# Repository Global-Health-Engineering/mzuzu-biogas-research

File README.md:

# Solar Sludge Pasteurization Control System

This repository contains the engineering files, firmware, and analysis scripts for a solar-powered sludge pasteurization system deployed in Mzuzu, Malawi. The system automates the thermal treatment of anaerobic digester effluent to ensure safe, pathogen-free discharge.

## Electronics Design
Hardware design files developed in KiCad.
- solar_pasteurization_controller: The main PCB project including schematics (mcu, power, solar_charger, actuators), PCB layout, and 3D models.
- simulations: SPICE simulations for the power switching circuitry.

## Microcontroller Software
Primary system firmware built using Zephyr RTOS.
- nucleo_l432kc_program_ert_algo: The production firmware implementing the retention time estimation algorithm. Needs to be tested.
- LoRa_TX / LoRa_RX: Simple LoRa scripts for testing. LoRa RX runs on the STM32L432KC eval-board that is connected to the research hut laptop.
- nucleo_l432kc_program_no_rtc: The production firmware implementing the threshold-based control logic.

## Arduino Software
Software that runs on the 2 Arduinos inside the Mzuzu research hut.
- luca_electronics: The software that runs on the microcontroller that's part of Luca Jakobs' biogas pasteurizer system.
- shared_plumbing_electronics: This pertains to the infrastructure electronics.

## Measurements
Data processing and experimental analysis scripts (Python).
- Heat Exchanger Efficiency: Scripts to calculate the h values and thermal efficiency from raw .csv data.
- espinosa_d_values: Logarithmic fit scripts for pathogen inactivation kinetics with data points taken from Deniz Cinar's paper.
- solcast_data_analysis: Analysis of solar irradiance data for the Mzuzu region.
- data_analysis_scripts: Contains the Python scripts for analyzing the .csv data files that can be found in the mzuzu-biogas-research git repo. That repo contains up-to-date data from the research site. 

## PC Software
High-level data handling and parsing for the research hut PC.
- nucleo_parser: Parses the USB packets sent by the LoRa RX microcontroller.
- edb_parser: Parses the USB packets sent by the infrastructure microcontroller. This is called *edb_parser* because it evolved from a simple automation of the EDB (effluent distribution) box.
- lj_parser: Parses the USB packets sent by the biogas pasteurization system microcontroller

For questions, please contact me through:
rcppolat@gmail.com

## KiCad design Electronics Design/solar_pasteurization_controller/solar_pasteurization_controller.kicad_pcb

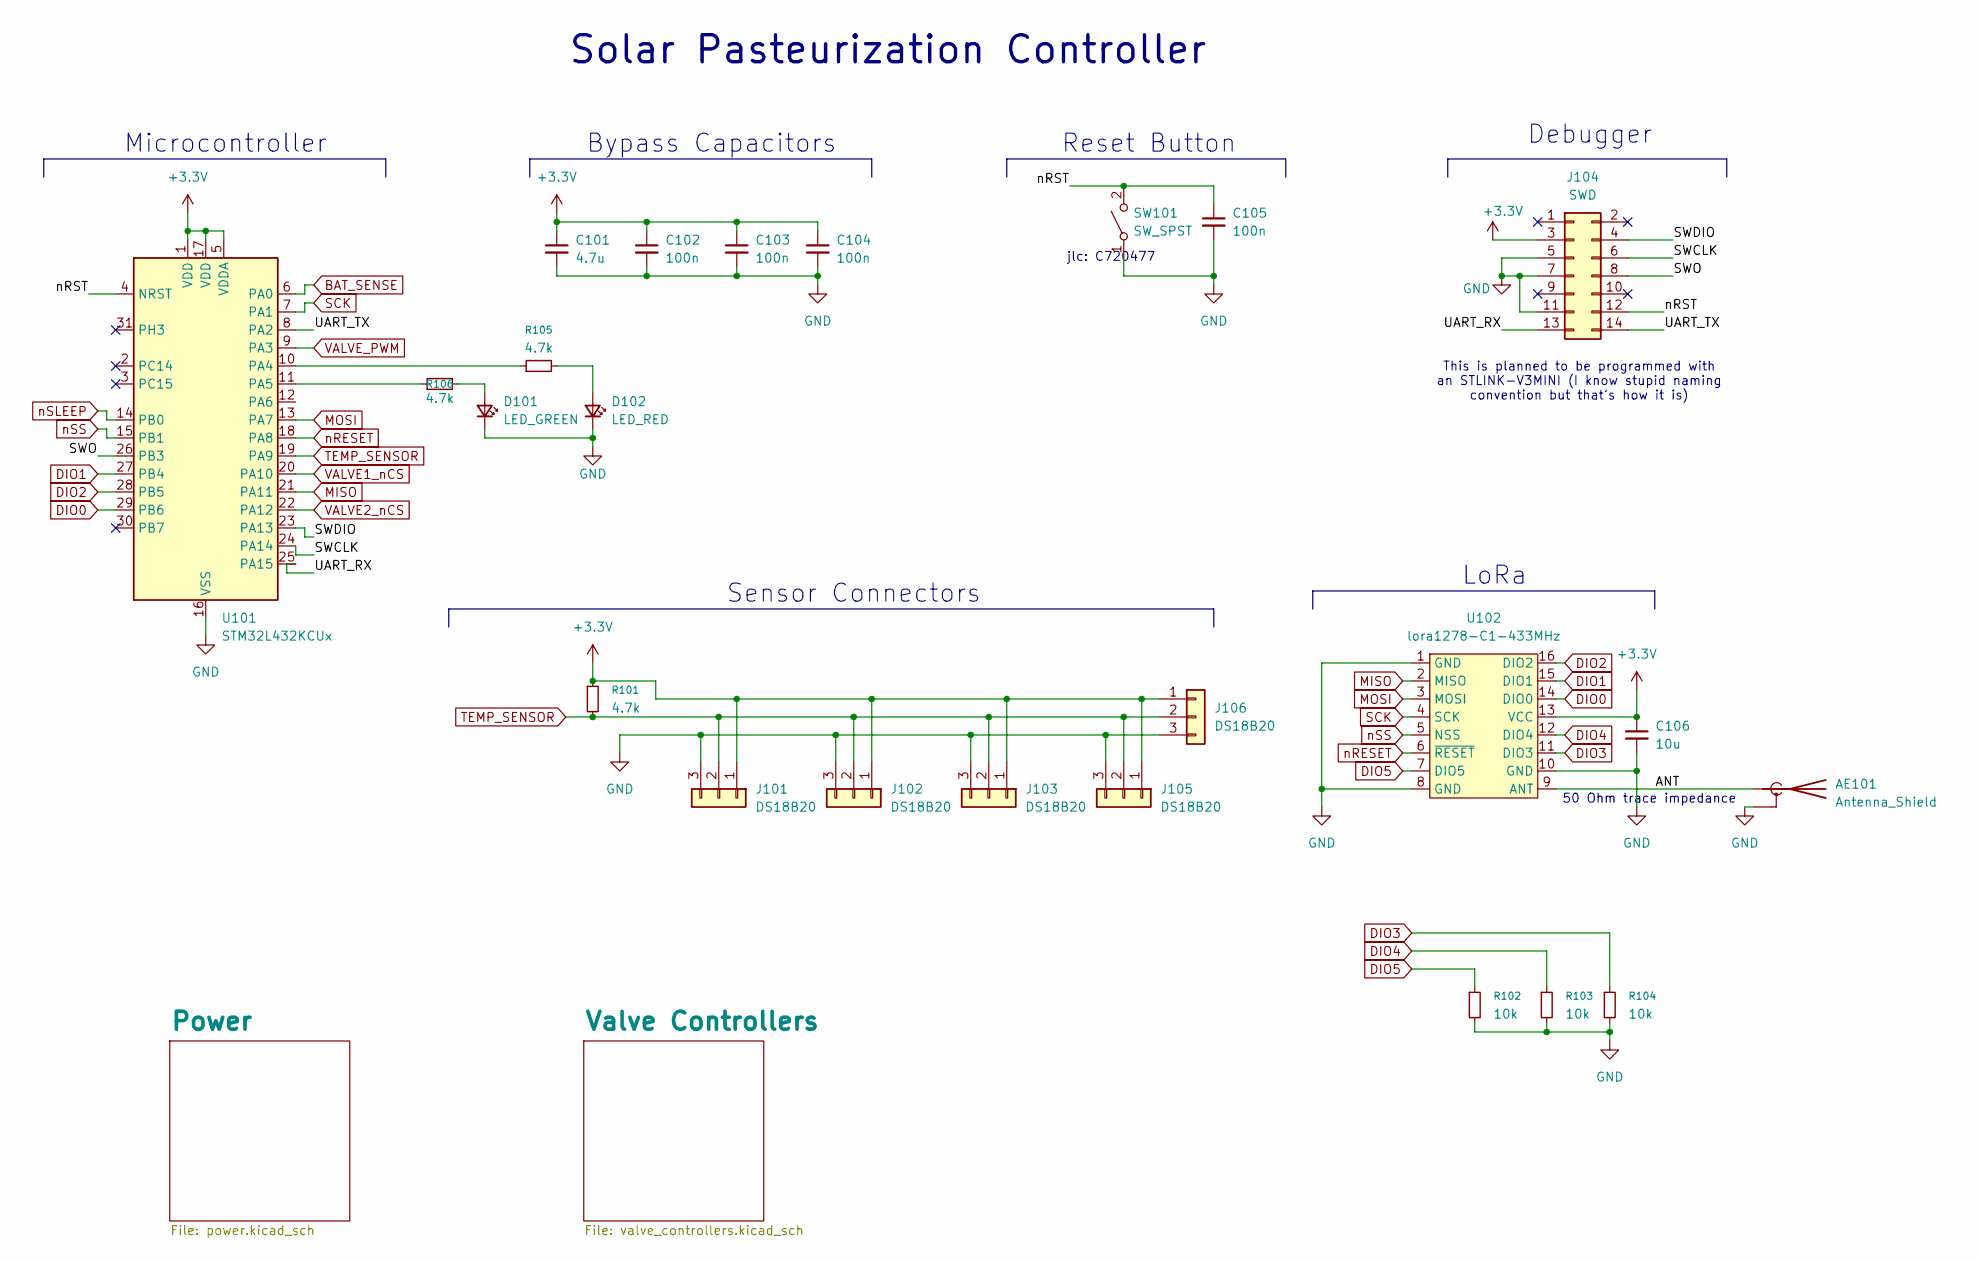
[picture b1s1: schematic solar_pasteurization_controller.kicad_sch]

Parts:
AE101: Antenna_Shield; SMA_Samtec_SMA-J-P-H-ST-EM1_EdgeMount; JLCPCB Part # C5301850
C101: 4.7u; C_0603_1608Metric; JLCPCB Part # C19666
C102, C103, C104, C105: 100n; C_0603_1608Metric; JLCPCB Part # C14663
C106: 10u; C_0603_1608Metric; JLCPCB Part # C96446
D101: LED_GREEN; LED_0805_2012Metric; JLCPCB Part # C2297
D102: LED_RED; LED_0805_2012Metric; JLCPCB Part # C84256
J101, J102, J103, J105, J106: DS18B20; Molex_PicoBlade_53048-0310_1x03_P1.25mm_Horizontal; JLCPCB Part # C505275
J104: SWD; PinHeader_2x07_P1.27mm_Vertical; JLCPCB Part # C2935955
R101, R105, R106: 4.7k; R_0603_1608Metric; JLCPCB Part # C23162
R102, R103, R104: 10k; R_0603_1608Metric; JLCPCB Part # C25804
SW101: SW_SPST; SW_SPST_TS-1088-xR025; JLCPCB Part # C720477
U101: STM32L432KCUx; QFN-32-1EP_5x5mm_P0.5mm_EP3.45x3.45mm; JLCPCB Part # C1337280
U102: lora1278-C1-433MHz; JLCPCB Part # C3001529

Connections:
+3.3V: C101.1, C102.1, C103.1, C104.1, C106.1, J101.1, J102.1, J103.1, J104.3, J105.1, J106.1, R101.1, U101.1 (VDD), U101.5 (VDDA), U101.17 (VDD), U102.13 (VCC); also elsewhere on the board
/ANT: AE101.1 (A), U102.9 (ANT)
/SWCLK: J104.6, U101.24 (PA14)
/SWDIO: J104.4, U101.23 (PA13)
/SWO: J104.8, U101.26 (PB3)
/UART_RX: J104.13, U101.25 (PA15)
/UART_TX: J104.14, U101.8 (PA2)
/nRST: C105.1, J104.12, SW101.2 (B), U101.4 (NRST)
BAT_SENSE: U101.6 (PA0); also elsewhere on the board
DIO0: U101.29 (PB6), U102.14 (DIO0)
DIO1: U101.27 (PB4), U102.15 (DIO1)
DIO2: U101.28 (PB5), U102.16 (DIO2)
DIO3: R104.1, U102.11 (DIO3)
DIO4: R103.1, U102.12 (DIO4)
DIO5: R102.1, U102.7 (DIO5)
GND: AE101.2 (Shield), C101.2, C102.2, C103.2, C104.2, C105.2, C106.2, D101.1 (K), D102.1 (K), J101.3, J102.3, J103.3, J104.5, J104.7, J104.11, J105.3, J106.3, R102.2, R103.2, R104.2, SW101.1 (A), U101.16 (VSS), U101.32 (VSS), U101.33 (VSS), U102.1 (GND), U102.8 (GND), U102.10 (GND); also elsewhere on the board
MISO: U101.21 (PA11), U102.2 (MISO); also elsewhere on the board
MOSI: U101.13 (PA7), U102.3 (MOSI); also elsewhere on the board
unnamed: D101.2 (A), R106.2
unnamed: D102.2 (A), R105.2
unnamed: R105.1, U101.10 (PA4)
unnamed: R106.1, U101.11 (PA5)
SCK: U101.7 (PA1), U102.4 (SCK); also elsewhere on the board
TEMP_SENSOR: J101.2, J102.2, J103.2, J105.2, J106.2, R101.2, U101.19 (PA9)
VALVE1_nCS: U101.20 (PA10); also elsewhere on the board
VALVE2_nCS: U101.22 (PA12); also elsewhere on the board
VALVE_PWM: U101.9 (PA3); also elsewhere on the board
nRESET: U101.18 (PA8), U102.6 (~RESET)
nSLEEP: U101.14 (PB0); also elsewhere on the board
nSS: U101.15 (PB1), U102.5 (NSS)

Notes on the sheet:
50 Ohm trace impedance
Microcontroller
Sensor Connectors
Debugger
Reset Button
Bypass Capacitors
This is planned to be programmed with an STLINK-V3MINI (I know stupid naming convention but that's how it is)
Solar Pasteurization Controller
LoRa
jlc: C720477

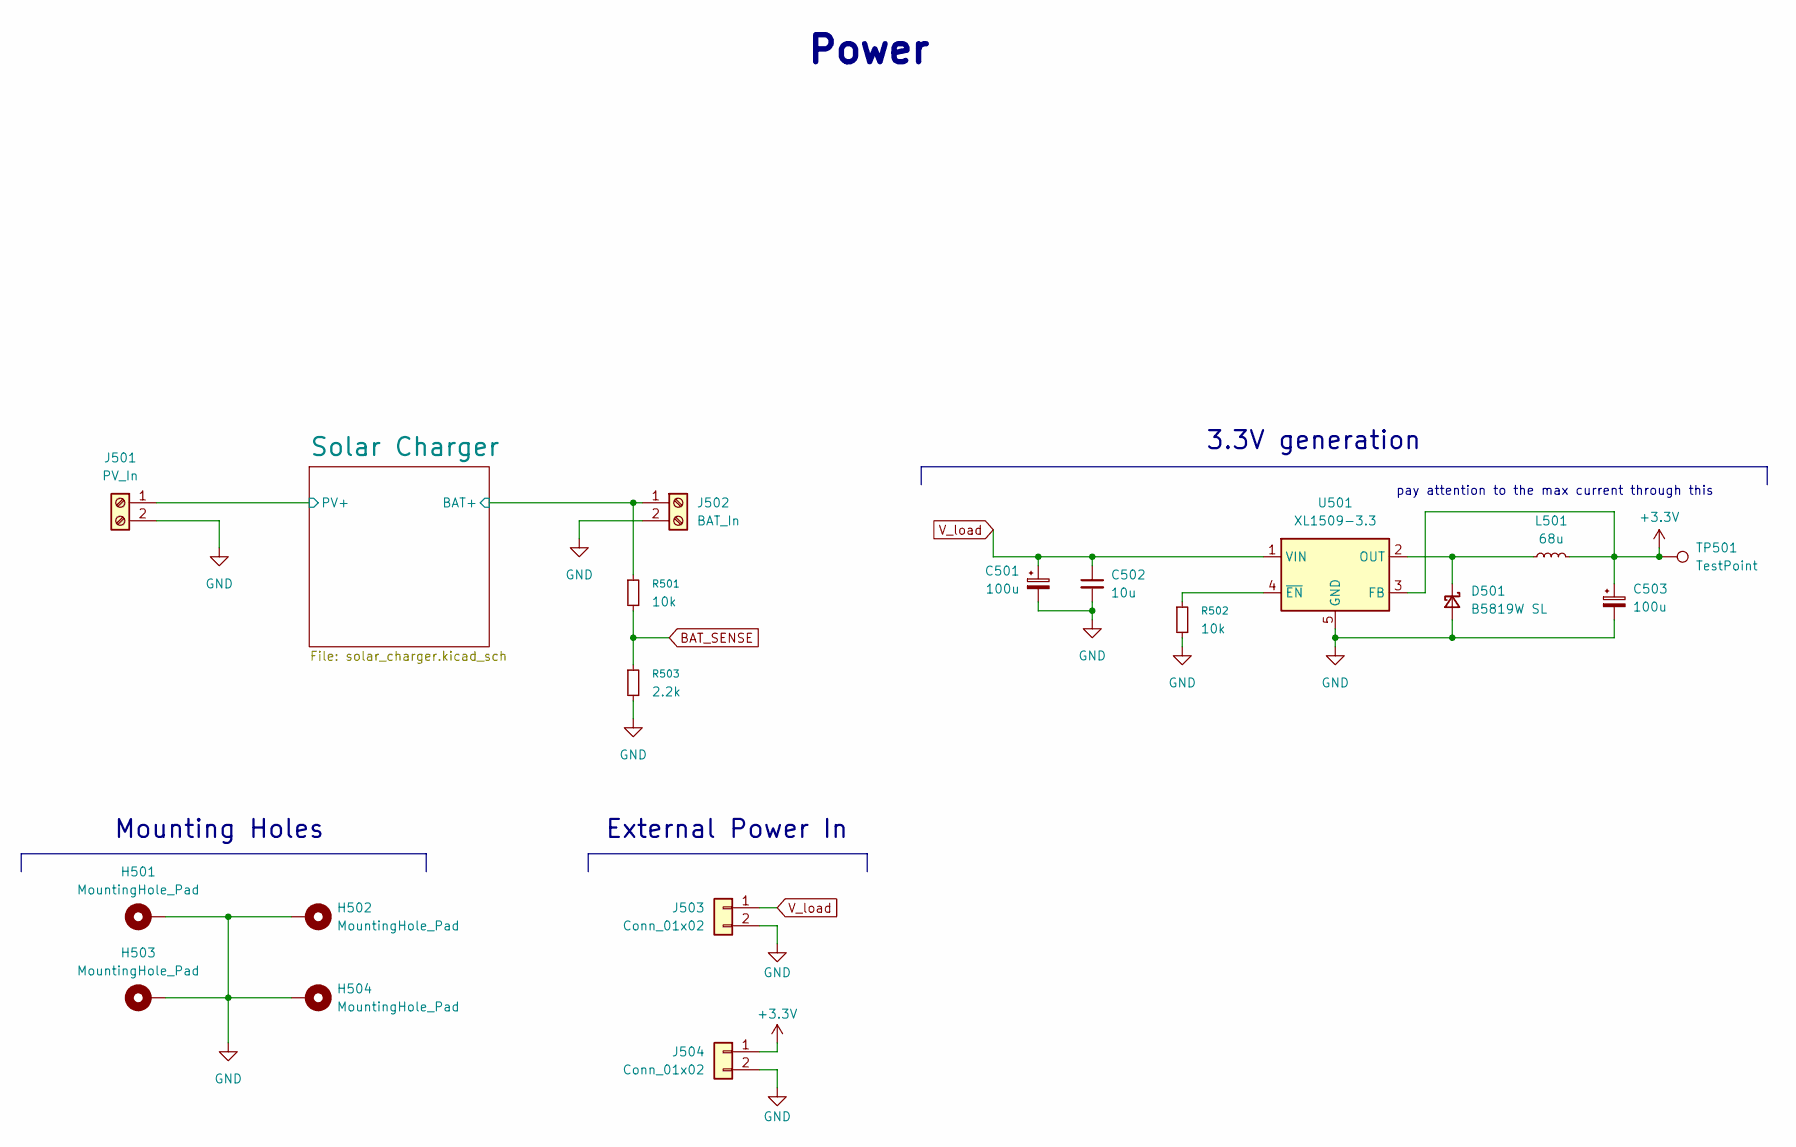
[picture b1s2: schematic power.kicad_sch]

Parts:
C501, C503: 100u; CP_Elec_6.3x5.9; LCSC_Part_Number C136277
C502: 10u; C_0603_1608Metric; LCSC_Part_Number C15525
D501: B5819W SL; D_SOD-123; LCSC_Part_Number C146713
H501, H502, H503, H504: MountingHole_Pad; MountingHole_2.7mm_M2.5_DIN965_Pad_TopBottom
J501: PV_In; AMASS_XT30PW-M_1x02_P2.50mm_Horizontal; JLCPCB Part # C431092
J502: BAT_In; AMASS_XT30PW-M_1x02_P2.50mm_Horizontal; JLCPCB Part # C431092
J503, J504: Conn_01x02; PinHeader_1x02_P2.54mm_Vertical
L501: 68u; L_Changjiang_FNR5040S; LCSC_Part_Number C167977
R501, R502: 10k; R_0603_1608Metric; LCSC_Part_Number C190095
R503: 2.2k; R_0603_1608Metric; JLCPCB Part # C4190
TP501: TestPoint; TestPoint_Pad_1.5x1.5mm
U501: XL1509-3.3; SOIC-8_3.9x4.9mm_P1.27mm; LCSC_Part_Number C2681226

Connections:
+3.3V: C503.1, J504.1, L501.2, TP501.1, U501.3 (FB); also elsewhere on the board
/Power/Solar Charger/PV+: J501.1; also elsewhere on the board
/Power/Solar Charger/V_bat: J502.1, R501.1; also elsewhere on the board
BAT_SENSE: R501.2, R503.1; also elsewhere on the board
GND: C501.2, C502.2, C503.2, D501.2 (A), H501.1, H502.1, H503.1, H504.1, J501.2, J502.2, J503.2, J504.2, R502.2, R503.2, U501.5 (GND), U501.6 (GND), U501.7 (GND), U501.8 (GND); also elsewhere on the board
unnamed: D501.1 (K), L501.1, U501.2 (OUT)
unnamed: R502.1, U501.4 (~EN)
V_load: C501.1, C502.1, J503.1, U501.1 (VIN); also elsewhere on the board

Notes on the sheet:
Power
External Power In
Mounting Holes
3.3V generation
pay attention to the max current through this

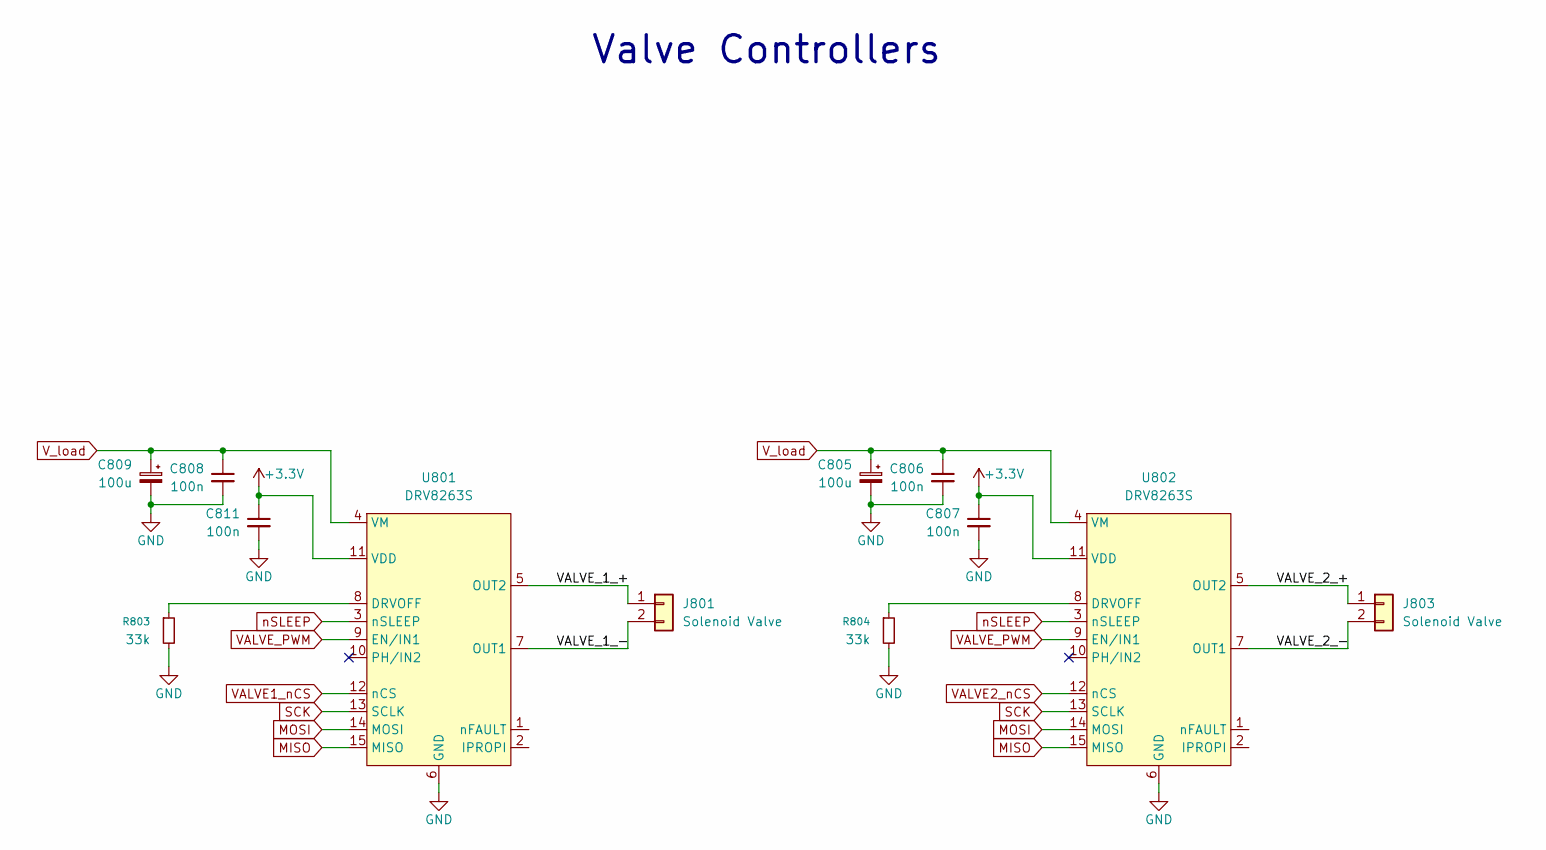
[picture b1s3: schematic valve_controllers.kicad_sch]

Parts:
C805, C809: 100u; CP_Elec_6.3x5.9; JLCPCB Part # C72478
C806, C807, C808, C811: 100n; C_0603_1608Metric; JLCPCB Part # C14663
J801, J803: Solenoid Valve; AMASS_XT30PW-M_1x02_P2.50mm_Horizontal; JLCPCB Part # C431092
R803, R804: 33k; R_0603_1608Metric; JLCPCB Part # C4216
U801, U802: DRV8263S; JLCPCB Part # C51893863

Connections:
+3.3V: C807.1, C811.1, U801.11 (VDD), U802.11 (VDD); also elsewhere on the board
/Valve Controllers/VALVE_1_+: J801.1, U801.5 (OUT2)
/Valve Controllers/VALVE_1_-: J801.2, U801.7 (OUT1)
/Valve Controllers/VALVE_2_+: J803.1, U802.5 (OUT2)
/Valve Controllers/VALVE_2_-: J803.2, U802.7 (OUT1)
GND: C805.2, C806.2, C807.2, C808.2, C809.2, C811.2, R803.2, R804.2, U801.6 (GND), U802.6 (GND); also elsewhere on the board
MISO: U801.15 (MISO), U802.15 (MISO); also elsewhere on the board
MOSI: U801.14 (MOSI), U802.14 (MOSI); also elsewhere on the board
unnamed: R803.1, U801.8 (DRVOFF)
unnamed: R804.1, U802.8 (DRVOFF)
SCK: U801.13 (SCLK), U802.13 (SCLK); also elsewhere on the board
VALVE1_nCS: U801.12 (nCS); also elsewhere on the board
VALVE2_nCS: U802.12 (nCS); also elsewhere on the board
VALVE_PWM: U801.9 (EN/IN1), U802.9 (EN/IN1); also elsewhere on the board
V_load: C805.1, C806.1, C808.1, C809.1, U801.4 (VM), U802.4 (VM); also elsewhere on the board
nSLEEP: U801.3 (nSLEEP), U802.3 (nSLEEP); also elsewhere on the board

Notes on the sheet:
Valve Controllers

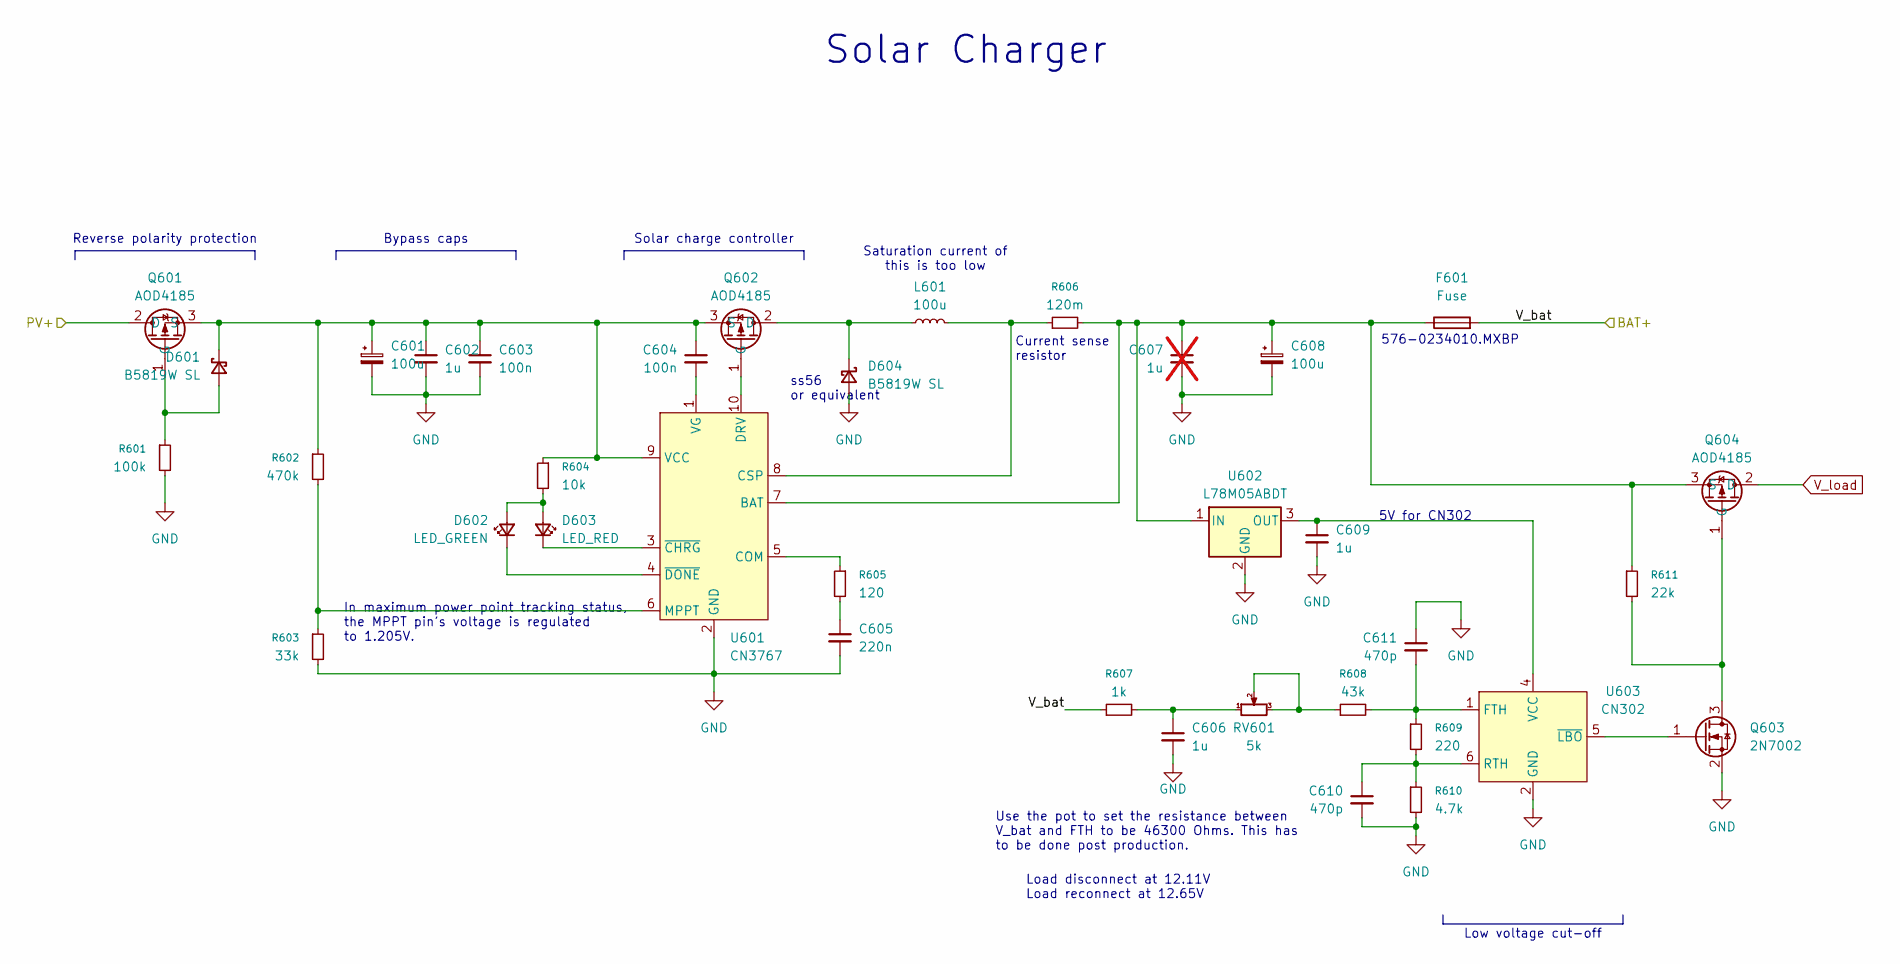
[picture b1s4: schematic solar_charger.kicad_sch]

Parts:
C601, C608: 100u; CP_Elec_6.3x5.9; JLCPCB Part # C72478
C602, C606, C609: 1u; C_0603_1608Metric; JLCPCB Part # C15849
C603, C604: 100n; C_0603_1608Metric; JLCPCB Part # C14663
C605: 220n; C_0603_1608Metric; JLCPCB Part # C21120
C607: 1u; C_0603_1608Metric; JLCPCB Part # C15849; not fitted
C610, C611: 470p; C_0603_1608Metric; JLCPCB Part # C1620
D601, D604: B5819W SL; D_SOD-123; JLCPCB Part # C8598
D602: LED_GREEN; LED_0805_2012Metric; JLCPCB Part # C2297
D603: LED_RED; LED_0805_2012Metric; JLCPCB Part # C84256
F601: Fuse; Fuseholder_Littelfuse_100_series_5x20mm; JLCPCB Part # C206887
L601: 100u; L_Changjiang_FNR5040S; JLCPCB Part # C167979
Q601, Q602, Q604: AOD4185; TO-252-2; JLCPCB Part # C400894
Q603: 2N7002; SOT-23; JLCPCB Part # C8545
R601: 100k; R_0603_1608Metric; JLCPCB Part # C25803
R602: 470k; R_0603_1608Metric; JLCPCB Part # C23178
R603: 33k; R_0603_1608Metric; JLCPCB Part # C4216
R604: 10k; R_0603_1608Metric; JLCPCB Part # C25804
R605: 120; R_0603_1608Metric; JLCPCB Part # C22787
R606: 120m; R_1206_3216Metric; JLCPCB Part # C24435
R607: 1k; R_0603_1608Metric; JLCPCB Part # C21190
R608: 43k; R_0603_1608Metric; JLCPCB Part # C23172
R609: 220; R_0603_1608Metric; JLCPCB Part # C22962
R610: 4.7k; R_0603_1608Metric; JLCPCB Part # C23162
R611: 22k; R_0603_1608Metric; JLCPCB Part # C31850
RV601: 5k; Potentiometer_Bourns_3386W_Horizontal; JLCPCB Part # C118907
U601: CN3767; SSOP-10_3.9x4.9mm_P1.00mm; JLCPCB Part # C81968
U602: L78M05ABDT; TO-252-2; JLCPCB Part # C58069
U603: CN302; SOT-23-6; JLCPCB Part # C32773

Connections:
/Power/Solar Charger/PV+: Q601.2 (D); also elsewhere on the board
/Power/Solar Charger/V_bat: F601.2, R607.1; also elsewhere on the board
GND: C601.2, C602.2, C603.2, C605.2, C606.2, C607.2, C608.2, C609.2, C610.2, C611.1, D604.2 (A), Q603.2 (S), R601.2, R603.2, R610.2, U601.2 (GND), U602.2 (GND), U603.2 (GND); also elsewhere on the board
unnamed: C605.1, R605.2
unnamed: C606.1, R607.2, RV601.1
unnamed: D601.2 (A), Q601.1 (G), R601.1
unnamed: C601.1, C602.1, C603.1, C604.1, D601.1 (K), Q601.3 (S), Q602.3 (S), R602.1, R604.1, U601.9 (VCC)
unnamed: D602.2 (A), D603.2 (A), R604.2
unnamed: D602.1 (K), U601.4 (~DONE)
unnamed: D603.1 (K), U601.3 (~CHRG)
unnamed: D604.1 (K), L601.1, Q602.2 (D)
unnamed: Q602.1 (G), U601.10 (DRV)
unnamed: Q603.3 (D), Q604.1 (G), R611.2
unnamed: Q603.1 (G), U603.5 (~LBO)
unnamed: C607.1, C608.1, F601.1, Q604.3 (S), R606.2, R611.1, U601.7 (BAT), U602.1 (IN)
unnamed: R608.1, RV601.2, RV601.3
unnamed: R605.1, U601.5 (COM)
unnamed: L601.2, R606.1, U601.8 (CSP)
unnamed: R602.2, R603.1, U601.6 (MPPT)
unnamed: C604.2, U601.1 (VG)
unnamed: C609.1, U602.3 (OUT), U603.4 (VCC)
unnamed: C611.2, R608.2, R609.1, U603.1 (FTH)
unnamed: C610.1, R609.2, R610.1, U603.6 (RTH)
V_load: Q604.2 (D); also elsewhere on the board

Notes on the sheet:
Current sense resistor
Low voltage cut-off
Solar Charger
Solar charge controller
Saturation current of this is too low
Reverse polarity protection
Use the pot to set the resistance between V_bat and FTH to be 46300 Ohms. This has to be done post production.
576-0234010.MXBP
In maximum power point tracking status, the MPPT pin's voltage is regulated to 1.205V.
5V for CN302
Load disconnect at 12.11V Load reconnect at 12.65V
ss56 or equivalent
Bypass caps

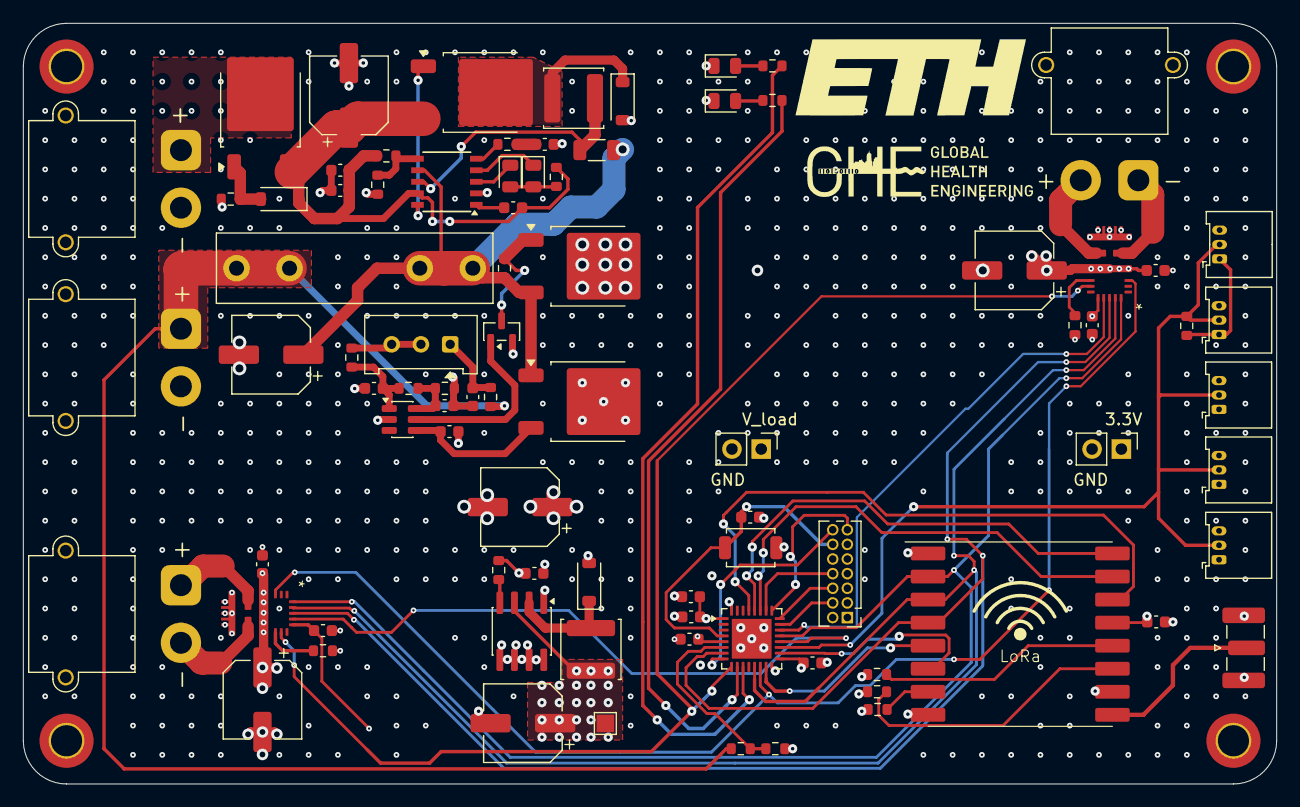
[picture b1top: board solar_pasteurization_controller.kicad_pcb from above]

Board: 4 copper layers, 108.8 x 66.0 mm, 89 parts (0 on the bottom side), 61 nets.

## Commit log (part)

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2026-04-10 Periodic CSV update
2026-05-27 transfered private git repo files to the ghe repo
2026-05-27 add license and citation
2026-05-27 add DOI
